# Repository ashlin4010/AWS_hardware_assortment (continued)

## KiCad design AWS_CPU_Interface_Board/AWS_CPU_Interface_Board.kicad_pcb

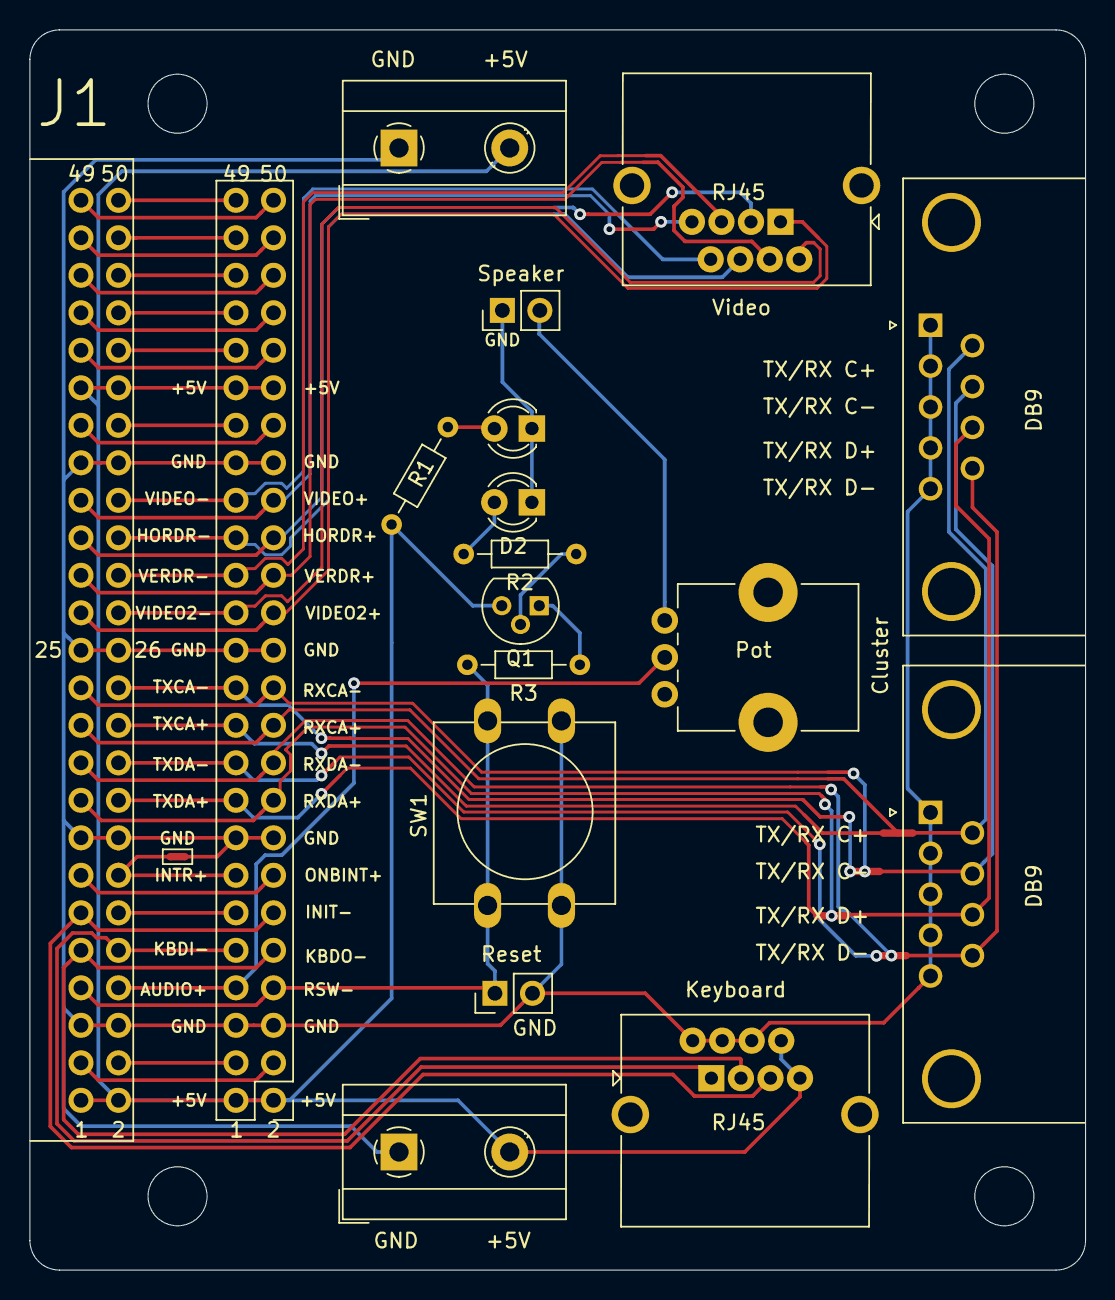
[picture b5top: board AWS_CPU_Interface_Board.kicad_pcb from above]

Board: 2 copper layers, 71.5 x 84.0 mm, 27 parts (0 on the bottom side), 49 nets.

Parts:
D1: LED; LED_D3.0mm
D2: Reset LED; LED_D3.0mm
H1, H2, H3, H4: MountingHole; MountingHole_4mm
J1: Conn_2Rows-50Pins; PinHeader_2x25_P2.54mm_Horizontal
J2: Speaker; PinHeader_1x02_P2.54mm_Vertical
J3, J6: Power; TerminalBlock_MetzConnect_Type171_RT13702HBWC_1x02_P7.50mm_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
J4, J5: Cluster; DSUB-9_Female_Horizontal_P2.77x2.84mm_EdgePinOffset7.70mm_H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
J7: Video; RJ45_aliexpress
J8: Keyboard; RJ45_aliexpress
J9: Reset_ex; PinHeader_1x02_P2.54mm_Vertical
J10: Conn_2Rows-50Pins; PinHeader_2x25_P2.54mm_Vertical
NT1, NT2, NT3, NT4: Net-Tie_3; NetTie-3_SMD_Pad0.5mm
NT5: Net-Tie_2; NetTie-2_SMD_Pad0.5mm
Q1: Q_PNP_BCE; TO-92
R1: 10k; R_Axial_DIN0204_L3.6mm_D1.6mm_P7.62mm_Horizontal
R2, R3: 1k; R_Axial_DIN0204_L3.6mm_D1.6mm_P7.62mm_Horizontal
RV1: Volume; Potentiometer_Bourns_PTV09A-1_Single_Vertical
SW1: Reset Switch; SW_PUSH-12mm

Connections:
+5V: J1.1, J1.2, J1.39, J1.40, J3.2, J6.2, J8.7, J8.8, J10.1, J10.2, J10.39, J10.40, Q1.3, R1.1
/U3: J1.3, J10.3
/U4: J1.4, J10.4
/U12: J1.12, J10.12
/U37: J1.37, J10.37
/U38: J1.38, J10.38
/U41: J1.41, J10.41
/U42: J1.42, J10.42
/U43: J1.43, J10.43
/U44: J1.44, J10.44
/U45: J1.45, J10.45
/U46: J1.46, J10.46
/U47: J1.47, J10.47
/U48: J1.48, J10.48
/U49: J1.49, J10.49
/U50: J1.50, J10.50
AUDIO+: J1.8, J10.8, RV1.2
GND: D1.1, D2.1, J1.5, J1.6, J1.15, J1.16, J1.25, J1.26, J1.35, J1.36, J2.1, J3.1, J4.1, J4.2, J4.3, J4.4, J4.5, J5.1, J5.2, J5.3, J5.4, J5.5, J6.1, J8.2, J8.4, J8.6, J9.2, J10.5, J10.6, J10.15, J10.16, J10.25, J10.26, J10.35, J10.36, NT5.2, SW1.2
HORDR+: J1.31, J7.3, J10.31
HORDR-: J1.32, J7.6, J10.32
INIT-: J1.11, J8.5, J10.11
INTR+: J1.14, J10.14, NT5.1
KBDI-: J1.10, J8.1, J10.10
KBDO-: J1.9, J8.3, J10.9
unnamed: D1.2, R1.2
unnamed: D2.2, R2.2
unnamed: J2.2, RV1.3
unnamed: J4.6, J5.6, NT4.3
unnamed: J4.7, J5.7, NT3.3
unnamed: J4.8, J5.8, NT2.3
unnamed: J4.9, J5.9, NT1.3
unnamed: Q1.1, R3.1
unnamed: Q1.2, R2.1
ONBINT+: J1.13, J10.13
RSW-: J1.7, J9.1, J10.7, R3.2, SW1.1
RXCA+: J1.21, J10.21, NT4.2
RXCA-: J1.23, J10.23, NT3.2
RXDA+: J1.17, J10.17, NT2.2
RXDA-: J1.19, J10.19, NT1.2
TXCA+: J1.22, J10.22, NT4.1
TXCA-: J1.24, J10.24, NT3.1
TXDA+: J1.18, J10.18, NT2.1
TXDA-: J1.20, J10.20, NT1.1
VERDR+: J1.29, J7.4, J10.29
VERDR-: J1.30, J7.5, J10.30
VIDEO+: J1.33, J7.7, J10.33
VIDEO-: J1.34, J7.8, J10.34
VIDEO_2+: J1.27, J7.1, J10.27
VIDEO_2-: J1.28, J7.2, J10.28

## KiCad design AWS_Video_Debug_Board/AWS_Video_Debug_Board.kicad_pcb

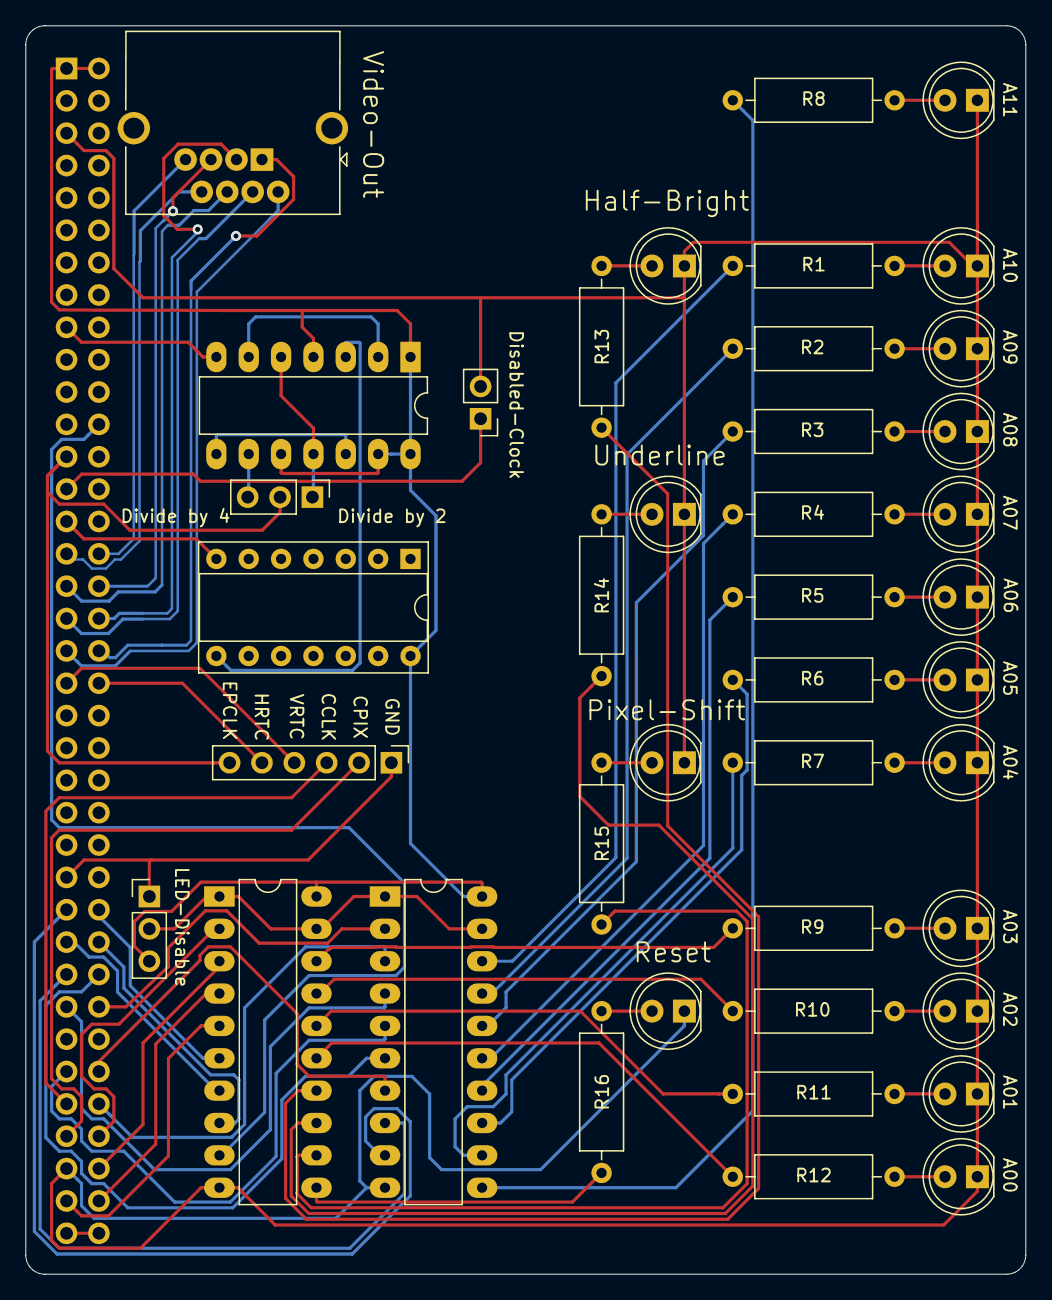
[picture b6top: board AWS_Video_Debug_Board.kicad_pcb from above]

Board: 2 copper layers, 78.5 x 98.0 mm, 42 parts (1 on the bottom side), 70 nets.

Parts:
D1, D2, D3, D4, D5, D6, D7, D8, D9, D10, D11, D12, D13, D14, D15, D16: LED_Small_ALT; LED_D5.0mm
J1: Video_Connector; PinSocket_2x37_P2.54mm_Vertical
J2: Video_Out; RJ45_aliexpress
J3: Video_Debug; PinHeader_1x06_P2.54mm_Vertical
JP1: Divide_2_4; PinHeader_1x03_P2.54mm_Vertical
JP2: Disable Clock; PinHeader_1x02_P2.54mm_Vertical
JP3: Disable_LED; PinHeader_1x03_P2.54mm_Vertical
R1, R2, R3, R4, R5, R6, R7, R8, R9, R10, R11, R12, R13, R14, R15, R16: 220R; R_Axial_DIN0309_L9.0mm_D3.2mm_P12.70mm_Horizontal
U1: 74LS74 (Flip-Flip); DIP-14_W7.62mm_LongPads
U2, U3: 74HCT541; DIP-20_W7.62mm_LongPads
X1: Socket; DIP-14_W7.62mm_Socket

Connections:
+5V: J1.1, J1.2, J1.73, J1.74, JP3.3, U1.1, U1.4, U1.10, U1.13, U1.14, U2.20, U3.20, X1.14
/AF: J1.53, U2.9
/BRIGHT_N: J1.32, J2.7
/BRIGHT_P: J1.31, J2.8
/CC0: J1.60, U2.2
/CC1: J1.66, U2.3
/CC2: J1.59, U2.4
/CC3: J1.63, U2.5
/CC4: J1.58, U2.6
/CC5: J1.64, U2.7
/CC6: J1.57, U2.8
/CCLK: J1.65, J3.3
/CPIX: J1.67, J3.2
/CPUDIS: J1.27, JP2.1
/EPCLK: J1.25, J3.6, JP1.2
/HB: J1.54, U3.6
/HBS: J1.56, U3.8
/HORDR_N: J1.36, J2.3
/HORDR_P: J1.35, J2.4
/HRTC: J1.40, J3.5
/LC0: J1.68, U3.2
/LC1: J1.70, U3.3
/LC2: J1.72, U3.4
/LC3: J1.71, U3.5
/LED_DIS: JP3.2, U2.1, U2.19, U3.1, U3.19
/RESET: J1.24, U3.9
/UL: J1.55, U3.7
/VERDR_N: J1.34, J2.5
/VERDR_P: J1.33, J2.6
/VIDEO_N: J1.38, J2.1
/VIDEO_P: J1.37, J2.2
/VRTC: J1.39, J3.4
GND: D1.1, D2.1, D3.1, D4.1, D5.1, D6.1, D7.1, D8.1, D9.1, D10.1, D11.1, D12.1, D13.1, D14.1, D15.1, D16.1, J1.5, J1.17, J1.29, J1.41, J1.51, J1.61, J1.69, J3.1, JP2.2, JP3.1, U1.7, U2.10, U3.10, X1.7
unnamed: D1.2, R1.1
unnamed: D2.2, R2.1
unnamed: D3.2, R3.1
unnamed: D4.2, R4.1
unnamed: D5.2, R5.1
unnamed: D6.2, R6.1
unnamed: D7.2, R7.1
unnamed: D8.2, R8.1
unnamed: D9.2, R9.1
unnamed: D10.2, R10.1
unnamed: D11.2, R11.1
unnamed: D12.2, R12.1
unnamed: D13.2, R13.1
unnamed: D14.2, R14.1
unnamed: D15.2, R15.1
unnamed: D16.2, R16.1
unnamed: JP1.1, U1.5, U1.11
unnamed: JP1.3, U1.9
unnamed: R1.2, U2.18
unnamed: R2.2, U2.17
unnamed: R3.2, U2.16
unnamed: R4.2, U2.15
unnamed: R5.2, U2.14
unnamed: R6.2, U2.13
unnamed: R7.2, U2.12
unnamed: R8.2, U2.11
unnamed: R9.2, U3.18
unnamed: R10.2, U3.17
unnamed: R11.2, U3.16
unnamed: R12.2, U3.15
unnamed: R13.2, U3.14
unnamed: R14.2, U3.13
unnamed: R15.2, U3.12
unnamed: R16.2, U3.11
unnamed: U1.2, U1.6
unnamed: U1.3, X1.8
unnamed: U1.8, U1.12

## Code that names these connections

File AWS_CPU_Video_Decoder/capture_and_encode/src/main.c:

#include <stdio.h>
#include <string.h>
#include <inttypes.h>
#include "pico/stdlib.h"
#include "hardware/dma.h"
#include "hardware/clocks.h"
#include "hardware/pio.h"
#include "decode.pio.h"
#include "video.pio.h"
#include "font/font.h"
#include "video.h"

#include "jkroso/gpio-interrupt.c"
#include "jkroso/encoder.c"
#include "jkroso/button.c"

// Capture pins
#define VSYNC_PIN 2
#define HSYNC_PIN 3
#define CCODE_PINS 4 // 4-11
#define CCLK_PIN 12

// Video output pins
#define DAC0 20
#define DAC1 21
#define DAC2 22

#define AWS_SCREEN_WIDTH 80
#define AWS_SCREEN_HEIGHT 29

// USB UART Settings
#define UART_ID uart0
#define BAUD_RATE 921600

extern uint16_t screen_data[];
int16_t line_offset = 0;
bool is_high_resolution = false;
rotary_encoder_t *encoder;

int dma_capture;
int dma_video;
int dma_restart;

// Video line buffers
volatile uint8_t active_buffer_index = 0;
uint8_t line_buffers[2][LINE_SIZE];
uint8_t *active_line = line_buffers[0];
uint8_t *inactive_line = line_buffers[0];


void onchange(rotary_encoder_t *encoder) {
    int16_t offset = encoder->position / 4;
    if (offset > 20) {
        offset = 20;
        encoder->position = 20 * 4;
    }
    if (offset < 0) {
        offset = 0;
        encoder->position = 0;
    }
    line_offset = offset;
}

void onpress(button_t *button) {
    is_high_resolution = button->state ? is_high_resolution : !is_high_resolution;
    line_offset = 0;
    encoder->position = 0;
}

// Called at the end of ever frame capture, re-trigger DMA
void dma_capture_irq_handler() {
    // Clear interrupt
    dma_hw->ints0 = 1u << dma_capture;

    // Reload DMA
    dma_channel_set_write_addr(
        dma_capture,
        screen_data,
        true
    );
}

// Called just before starting the next scanline
void dma_video_restart_irq_handler() {
    // Clear interrupt
    dma_hw->ints1 = 1u << dma_restart;

    // Switch active line buffer
    active_buffer_index ^= 1;
    active_line = line_buffers[active_buffer_index];
    inactive_line = line_buffers[active_buffer_index];

    // Build the next scan line
    write_scanline(inactive_line);
}

int main() {
    set_sys_clock_khz(125000, true);
    stdio_init_all();
    uart_init(UART_ID, BAUD_RATE);

    // Setup video
    video_init();
    // fill_screen_with_character(0x05, 0);
    fill_screen_with_character(0, 0);

    PIO pio_capture = pio0; // Use PIO0 for capture of video data
    PIO pio_video = pio1;  // Use PIO1 for video

    // -------------------------------
    // Load All Programs in PIO memory
    // -------------------------------
    uint offset_capture = pio_add_program(pio_capture, &capture_program);
    uint offset_raster  = pio_add_program(pio_capture, &raster_program);
    uint offset_vsync   = pio_add_program(pio_capture, &vsync_program);
    uint offset_video   = pio_add_program(pio_video, &video_program);

    // -------------------------------
    // Allocate State Machines
    // -------------------------------
    uint sm_capture = pio_claim_unused_sm(pio_capture, true);
    uint sm_raster  = pio_claim_unused_sm(pio_capture, true);
    uint sm_vsync   = pio_claim_unused_sm(pio_capture, true);
    uint sm_video   = pio_claim_unused_sm(pio_video, true);

    // -------------------------------
    // PIO Program Init
    // -------------------------------
    capture_program_init(pio_capture, sm_capture, offset_capture, CCODE_PINS);
    raster_program_init(pio_capture, sm_raster, offset_raster, HSYNC_PIN);
    vsync_program_init(pio_capture, sm_vsync, offset_vsync, VSYNC_PIN);
    video_program_init(pio_video, sm_video, offset_video, DAC0);

    // Get DMA channels
    dma_capture = dma_claim_unused_channel(true);
    dma_video = dma_claim_unused_channel(true);
    dma_restart = dma_claim_unused_channel(true);

    // -------------------------------
    // DMA Capture
    // -------------------------------
    dma_channel_config dma_capture_cf = dma_channel_get_default_config(dma_capture);
    channel_config_set_transfer_data_size(&dma_capture_cf, DMA_SIZE_16);  // Copy one full word
    channel_config_set_read_increment(&dma_capture_cf, false); // Read from the PIO output buffer
    channel_config_set_write_increment(&dma_capture_cf, true); // Write to RAM
    channel_config_set_dreq(&dma_capture_cf, pio_get_dreq(pio_capture, sm_capture, false));

    dma_channel_configure(
        dma_capture,
        &dma_capture_cf,
        screen_data,                            // Write address
        &pio_capture->rxf[sm_capture],          // Read address (the address of the pio's fifo)
        AWS_SCREEN_WIDTH * AWS_SCREEN_HEIGHT,   // Number of transfers
        false                                   // Autostart
    );

    // Tirgger a irq at the end of the read
    dma_channel_set_irq0_enabled(dma_capture, true);
    irq_set_exclusive_handler(DMA_IRQ_0, dma_capture_irq_handler);
    irq_set_enabled(DMA_IRQ_0, true);

    // -------------------------------
    // DMA Video Raster
    // -------------------------------
    dma_channel_config c0 = dma_channel_get_default_config(dma_video);
    channel_config_set_transfer_data_size(&c0, DMA_SIZE_8);  // One byte at a time
    channel_config_set_read_increment(&c0, true);
    channel_config_set_write_increment(&c0, false);
    channel_config_set_dreq(&c0, pio_get_dreq(pio_video, sm_video, true)); // Send byte as pio needs it
    channel_config_set_chain_to(&c0, dma_restart); // On the end of DMA0 start DMA1

    dma_channel_configure(
        dma_video,
        &c0,
        &pio_video->txf[sm_video],  // Write address (the address of the pio's fifo)
        line_blank_field,           // Address of the data to be read
        LINE_SIZE,                  // Number of transfers
        false                       // Autostart
    );

    // -------------------------------
    // DMA Video Chain
    // -------------------------------
    dma_channel_config c1 = dma_channel_get_default_config(dma_restart);
    channel_config_set_transfer_data_size(&c1, DMA_SIZE_32);    // Size of a pointer
    channel_config_set_read_increment(&c1, false);              // Read the same address
    channel_config_set_write_increment(&c1, false);             // Write the same address
    channel_config_set_chain_to(&c1, dma_video);                // On the end of DMA1 start DMA0

    dma_channel_configure(
        dma_restart,
        &c1,
        &dma_hw->ch[dma_video].read_addr,
        &active_line,
        1, // Move just the pointer
        false
    );

    // Tirgger an irq at the end of the "restart" transfer
    dma_channel_set_irq1_enabled(dma_restart, true);
    irq_set_exclusive_handler(DMA_IRQ_1, dma_video_restart_irq_handler);
    irq_set_enabled(DMA_IRQ_1, true);

    // -------------------------------
    // Start DMA and PIO
    // -------------------------------
    dma_start_channel_mask(1u << dma_restart); // Start video chain
    dma_start_channel_mask(1u << dma_capture); // Start capture

    capture_program_init(pio_capture, sm_capture, offset_capture, CCODE_PINS);
    raster_program_init(pio_capture, sm_raster, offset_raster, HSYNC_PIN);
    vsync_program_init(pio_capture, sm_vsync, offset_vsync, VSYNC_PIN);


    // Debug screen
    #if 0
    printf("\033[?25l");  // hide cursor
    while (1) {
        // Print capture
        printf("\033[H"); // just move to top-left
        putchar('\n');
        printf("+--------------------------------------------------------------------------------+\n");

        for(uint i = 0; i < 29; i++) {
            putchar('|');
            for(uint j = 0; j < SCREEN_WIDTH; j++) {
                uint index = (i * SCREEN_WIDTH) + j;
                uint16_t code = screen_data[index];
                uint8_t ac = 0x0F & (uint8_t)(code >> 8);
                uint8_t cc = (uint8_t)(code & 0xFF);

                if ((cc >= 32 && cc <= 126) || cc >= 128) {
                    putchar(cc);
                } else {
                    putchar(' ');
                }
            }
            putchar('|');
            printf("\n");
        }
        printf("+--------------------------------------------------------------------------------+\n\n");
    }
    #endif

    encoder = create_encoder(27, 28, onchange);
    button_t *button = create_button(26, onpress);
    while (true) tight_loop_contents();

    // Clean up
    pio_remove_program_and_unclaim_sm(&vsync_program, pio_capture, sm_vsync, offset_vsync);
    pio_remove_program_and_unclaim_sm(&raster_program, pio_capture, sm_raster, offset_raster);
    pio_remove_program_and_unclaim_sm(&capture_program, pio_capture, sm_capture, offset_capture);
    pio_remove_program_and_unclaim_sm(&video_program, pio_video, sm_video, offset_video);

    return 0;
}

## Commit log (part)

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2025-11-15 Clean up
2025-11-16 Added start of video decoader board
2025-12-29 Start of video board
2025-12-29 Update old motherboard for testing
2026-01-16 Update PCB to fix floppy drive & update video software to capure all the screen
2026-01-23 Added basic video
2026-01-24 double density
2026-01-24 Clean up before DMA rewrite
2026-01-24 Added chaining
2026-01-24 Fixed video output
2026-01-24 Fix level shifters
2026-01-24 Add gurber
2026-01-24 Added Schottky Diode
2026-01-25 Update CCLK pin
2026-01-25 Add attribute codes
2026-01-30 Draw from ram
2026-01-31 Fixed rendering issue
2026-02-01 Added DMA to video capture
2026-02-01 New project to combine capture and video
2026-02-01 Working
